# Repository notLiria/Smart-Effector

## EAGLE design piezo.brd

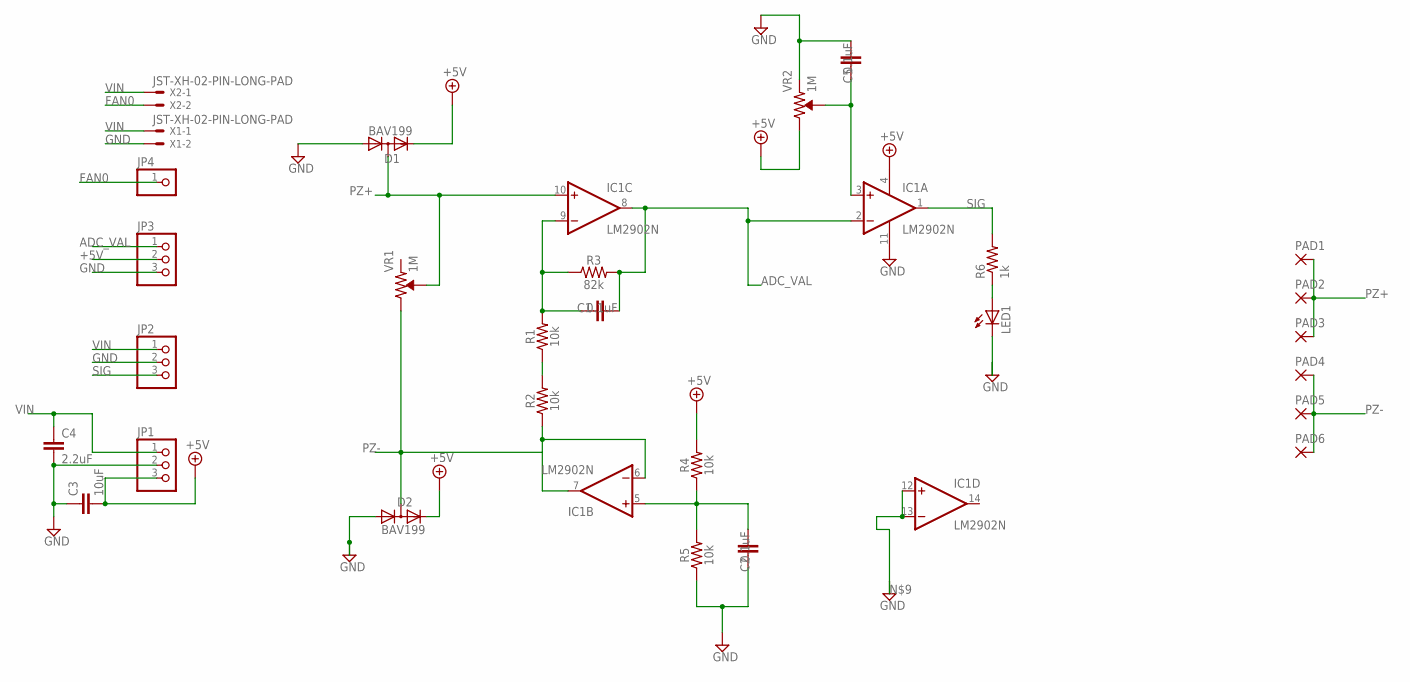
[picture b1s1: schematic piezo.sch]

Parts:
C1, C2, C5: 0.1uF; C025-024X044
C3: 10uF; C2.5-3
C4: 2.2uF; C2.5-3
D1, D2: BAV199; SOT23
IC1: LM2902N; DIL14
JP1, JP2, JP3: PINHD-1X3; 1X03
JP4: PINHD-1X1; 1X01
LED1: LED5MM
PAD1, PAD2, PAD3, PAD4, PAD5, PAD6: 1,6/0,8
R1, R2, R4, R5: 10k; AXIAL-0.3
R3: 82k; AXIAL-0.3
R6: 1k; 0207/9
VR1, VR2: 1M; TRIMPOT-SMD-TC33X
X1, X2: JST-XH-02-PIN-LONG-PAD; JST-XH-02-PACKAGE-LONG-PAD

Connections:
+5V: C3.2, D1.2 (C), D2.2 (C), IC1.4 (V+), JP1.3, JP3.2, R4.P$2 (2), VR2.1 (CW)
ADC_VAL: C1.2, IC1.2 (-IN), IC1.8 (OUT), JP3.1, R3.P$2 (2)
FAN0: JP4.1, X2.2
GND: C2.1, C3.1, C4.2, D1.1 (A), D2.1 (A), IC1.11 (V-), JP1.2, JP2.2, JP3.3, LED1.K (C), R5.P$1 (1), X1.2
unnamed: R1.P$1 (1), R2.P$2 (2)
unnamed: C1.1, IC1.9 (-IN), R1.P$2 (2), R3.P$1 (1)
unnamed: LED1.A, R6.1
unnamed: C2.2, IC1.5 (+IN), R4.P$1 (1), R5.P$2 (2)
unnamed: C5.1, IC1.3 (+IN), VR2.2 (WIPER)
unnamed: C5.2, VR2.3 (CCW)
unnamed: IC1.12 (+IN), IC1.13 (-IN)
PZ+: D1.3 (AC), IC1.10 (+IN), PAD1.1, PAD2.1, PAD3.1, VR1.2 (WIPER)
PZ-: D2.3 (AC), IC1.6 (-IN), IC1.7 (OUT), PAD4.1, PAD5.1, PAD6.1, R2.P$1 (1), VR1.1 (CW)
SIG: IC1.1 (OUT), JP2.3, R6.2
VIN: C4.1, JP1.1, JP2.1, X1.1, X2.1

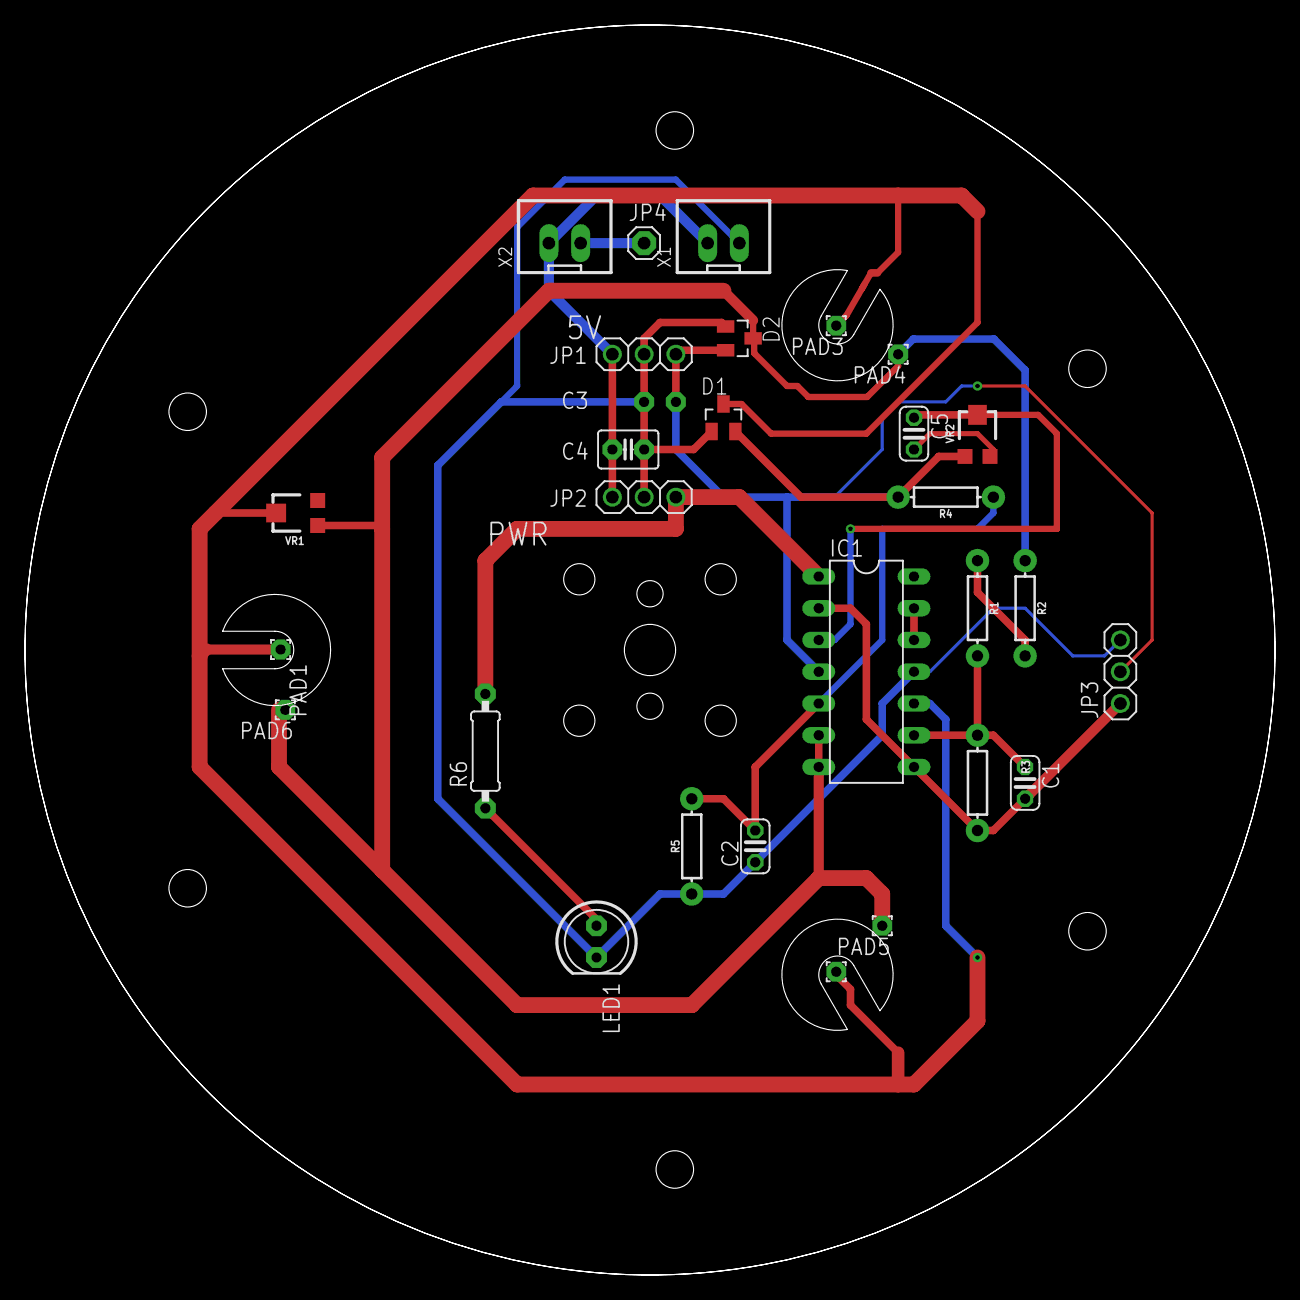
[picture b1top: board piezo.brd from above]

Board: 2 copper layers, 100.0 x 100.0 mm, 29 parts (1 on the bottom side), 15 nets.

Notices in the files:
parts and their libraries:
SparkFun-Resistors: Licensing: Creative Commons ShareAlike 4.0 International - https://creativecommons.org/licenses/by-sa/4.0
